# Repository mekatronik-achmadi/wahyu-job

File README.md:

This example test toolkit for various RF module.

###### SIM7000E
- [x] Own VDD
- [x] Serial Comm
- [x] Serial Prog
- [x] SIM Card Slot
- [x] GPS Antena
- [x] RF Antena
- [x] Boot-Config Pin
- [x] USB Firmware (R-USB Optional)
- [x] UART-FT232RL
- [x] UART-ESP32

###### ESP32-WROVER-IB
- [x] Own VDD
- [x] Serial Comm
- [x] Serial Prog
- [x] Boot-Config Pin
- [x] RTS-CTS Transistor
- [x] UART-FT232RL
- [x] UART-SIM7000

###### LORA SX1262
- [ ] Own VDD
- [ ] Serial Comm
- [ ] Serial Prog
- [ ] Boot-Config Pin

###### SIM800C
- [ ] Own VDD
- [ ] Serial Comm
- [ ] Serial Prog
- [ ] GPS Antena
- [ ] RF Antena
- [ ] Boot-Config Pin

###### FT232RL
- [x] Global VDD
- [x] Serial Comm
- [x] USB Port
- [x] UART Indicator (Optional)

###### AMS1117-3V3
- [x] Global VDD
- [x] Global VCC
- [x] VDD Selector

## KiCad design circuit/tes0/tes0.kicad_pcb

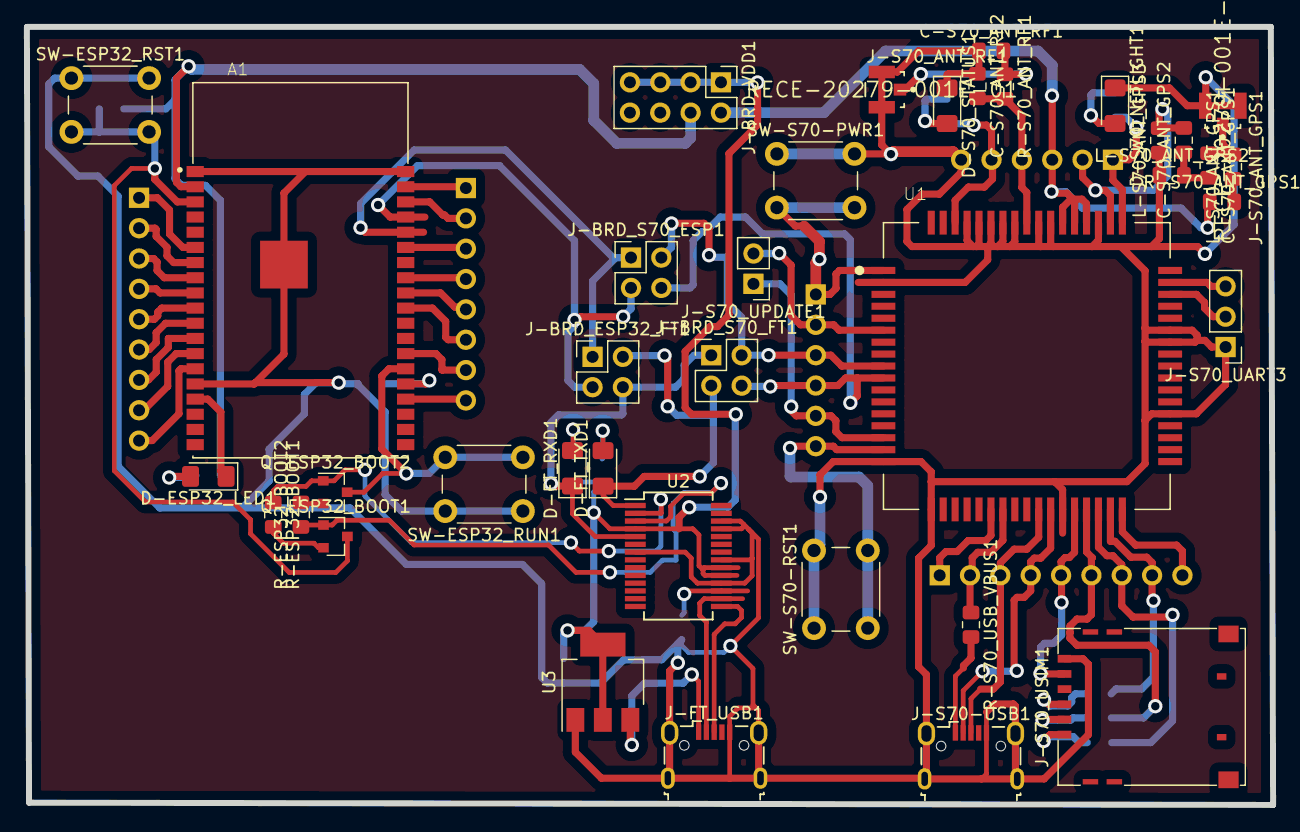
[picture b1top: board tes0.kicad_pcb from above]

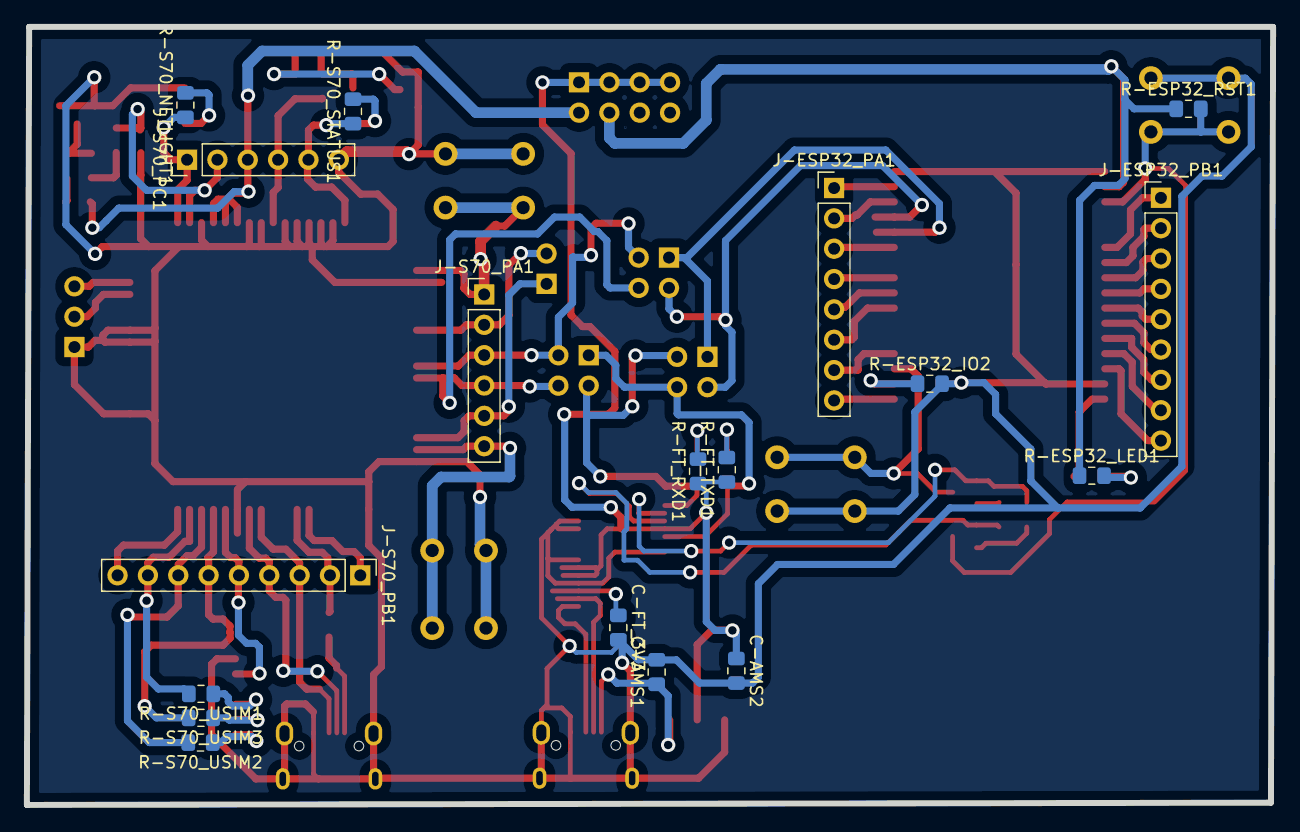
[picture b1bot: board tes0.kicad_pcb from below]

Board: 2 copper layers, 104.3 x 65.1 mm, 56 parts (18 on the bottom side), 71 nets.

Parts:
A1: ESP32-WROVER-I; XCVR_ESP32-WROVER-I
C-AMS1, C-AMS2: 100nF; C_0805_2012Metric_Pad1.15x1.40mm_HandSolder
C-FT_3V3: 100nF; C_0805_2012Metric_Pad1.15x1.40mm_HandSolder
C-S70_ANT_GPS1, C-S70_ANT_GPS2: 33pF; C_0805_2012Metric_Pad1.15x1.40mm_HandSolder
C-S70_ANT_RF1, C-S70_ANT_RF2: C; C_0805_2012Metric_Pad1.15x1.40mm_HandSolder
D-ESP32_LED1: LED; LED_1206_3216Metric_Pad1.42x1.75mm_HandSolder
D-FT_RXD1: LED; LED_1206_3216Metric_Pad1.42x1.75mm_HandSolder
D-FT_TXD1: LED; LED_1206_3216Metric_Pad1.42x1.75mm_HandSolder
D-S70_NETLIGHT1, D-S70_STATUS1: LED; LED_1206_3216Metric_Pad1.42x1.75mm_HandSolder
J-BRD_ESP32_FT1: Conn_02x02_Odd_Even; PinHeader_2x02_P2.54mm_Vertical
J-BRD_S70_ESP1, J-BRD_S70_FT1: Conn_02x02_Odd_Even; PinHeader_2x02_P2.54mm_Vertical
J-BRD_VDD1: Conn_02x04_Odd_Even; PinHeader_2x04_P2.54mm_Vertical
J-ESP32_PA1: Conn_01x08; PinHeader_1x08_P2.54mm_Vertical
J-ESP32_PB1: Conn_01x09; PinHeader_1x09_P2.54mm_Vertical
J-FT_USB1: USB_B_Micro; USB_Micro-B_Wuerth_629105150521
J-S70-USB1: USB_B_Micro; USB_Micro-B_Wuerth_629105150521
J-S70_ANT_GPS1, J-S70_ANT_RF1: RECE-20279-001E-01; Taoglas-RECE-20279-001E-01-MFG
J-S70_PA1, J-S70_PC1: Conn_01x06; PinHeader_1x06_P2.54mm_Vertical
J-S70_PB1: Conn_01x09; PinHeader_1x09_P2.54mm_Vertical
J-S70_UART3: Conn_01x03; PinHeader_1x03_P2.54mm_Vertical
J-S70_UPDATE1: Conn_01x02; PinHeader_1x02_P2.54mm_Vertical
J-S70_USIM1: SIM_Card; microSIM_JAE_SF53S006VCBR2000
L-S70_ANT_GPS1: 47nH; L_0805_2012Metric_Pad1.15x1.40mm_HandSolder
L-S70_ANT_GPS2, L-S70_ANT_GPS3: L; L_0805_2012Metric_Pad1.15x1.40mm_HandSolder
Q-ESP32_BOOT1, Q-ESP32_BOOT2: 2N3904; SOT-23
R-ESP32_BOOT1, R-ESP32_BOOT2: 100; R_0805_2012Metric_Pad1.15x1.40mm_HandSolder
R-ESP32_IO2, R-ESP32_RST1: 10K; R_0805_2012Metric_Pad1.15x1.40mm_HandSolder
R-ESP32_LED1: 330; R_0805_2012Metric_Pad1.15x1.40mm_HandSolder
R-FT_RXD1: 330; R_0805_2012Metric_Pad1.15x1.40mm_HandSolder
R-FT_TXD1: 330; R_0805_2012Metric_Pad1.15x1.40mm_HandSolder
R-S70_ANT_GPS1: 10; R_0805_2012Metric_Pad1.15x1.40mm_HandSolder
R-S70_ANT_RF1, R-S70_USB_VBUS1: 0; R_0805_2012Metric_Pad1.15x1.40mm_HandSolder
R-S70_NETLIGHT1, R-S70_STATUS1: 330; R_0805_2012Metric_Pad1.15x1.40mm_HandSolder
R-S70_USIM1, R-S70_USIM2, R-S70_USIM3: 22; R_0805_2012Metric_Pad1.15x1.40mm_HandSolder
SW-ESP32_RST1, SW-ESP32_RUN1: SW_Push; SW_PUSH_6mm
SW-S70-PWR1, SW-S70-RST1: SW_Push; SW_PUSH_6mm
U1: SIM7000E; SIMCON_SIM7000E
U2: FT232RL; SSOP-28_5.3x10.2mm_P0.65mm
U3: AMS1117-3.3; SOT-223-3_TabPin2

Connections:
/ESP32_BOOT: A1.25, Q-ESP32_BOOT2.3, SW-ESP32_RUN1.2
/ESP32_IO4: A1.26, J-ESP32_PA1.7
/ESP32_IO5: A1.29, J-ESP32_PA1.6
/ESP32_IO12: A1.14, J-ESP32_PB1.9
/ESP32_IO14: A1.13, J-ESP32_PB1.8
/ESP32_IO15: A1.23, J-ESP32_PA1.8
/ESP32_IO18: A1.30, J-ESP32_PA1.5
/ESP32_IO19: A1.31, J-ESP32_PA1.4
/ESP32_IO21: A1.33, J-ESP32_PA1.3
/ESP32_IO22: A1.36, J-ESP32_PA1.2
/ESP32_IO23: A1.37, J-ESP32_PA1.1
/ESP32_IO25: A1.10, J-ESP32_PB1.5
/ESP32_IO26: A1.11, J-ESP32_PB1.6
/ESP32_IO27: A1.12, J-ESP32_PB1.7
/ESP32_IO32: A1.8, J-ESP32_PB1.3
/ESP32_IO33: A1.9, J-ESP32_PB1.4
/ESP32_IO34: A1.6, J-ESP32_PB1.1
/ESP32_IO35: A1.7, J-ESP32_PB1.2
/ESP32_LED: A1.16, D-ESP32_LED1.1
/ESP32_RST: A1.3, Q-ESP32_BOOT1.3, R-ESP32_RST1.2, SW-ESP32_RST1.2
/ESP32_RXD: A1.34, J-BRD_ESP32_FT1.1, J-BRD_S70_ESP1.1
/ESP32_TXD: A1.35, J-BRD_ESP32_FT1.3, J-BRD_S70_ESP1.3
/ESP32_VDD: A1.2, J-BRD_VDD1.4, R-ESP32_LED1.1, R-ESP32_RST1.1
/FT_DTR: Q-ESP32_BOOT2.1, R-ESP32_BOOT1.1, U2.2
/FT_RTS: Q-ESP32_BOOT1.1, R-ESP32_BOOT2.1, U2.3
/FT_RXD: D-FT_RXD1.1, J-BRD_ESP32_FT1.4, J-BRD_S70_FT1.1, U2.5
/FT_TXD: D-FT_TXD1.1, J-BRD_ESP32_FT1.2, J-BRD_S70_FT1.3, U2.1
/S70_ANT_GPS: C-S70_ANT_GPS2.2, J-S70_PC1.2, L-S70_ANT_GPS3.2, U1.53
/S70_ANT_RF: C-S70_ANT_RF2.2, J-S70_PC1.4, R-S70_ANT_RF1.2, U1.60
/S70_BOOTCFG: J-S70_PA1.2, J-S70_UPDATE1.2, U1.6
/S70_GPIO0: J-S70_UART3.3, U1.50
/S70_GPIO1: J-S70_UART3.2, U1.49
/S70_MDMLOG_TX: J-S70_PB1.1, U1.23
/S70_NETLIGHT: J-S70_PC1.1, R-S70_NETLIGHT1.1, U1.52
/S70_NRST: J-S70_PA1.6, SW-S70-RST1.2, U1.16
/S70_PWRKEY: J-S70_PA1.1, SW-S70-PWR1.2, U1.1
/S70_RXD: J-BRD_S70_ESP1.4, J-BRD_S70_FT1.4, J-S70_PA1.4, U1.10
/S70_STATUS: J-S70_PC1.5, R-S70_STATUS1.1, U1.66
/S70_TXD: J-BRD_S70_ESP1.2, J-BRD_S70_FT1.2, J-S70_PA1.3, U1.9
/S70_USB_DM: J-S70-USB1.2, J-S70_PB1.4, U1.28
/S70_USB_DP: J-S70-USB1.3, J-S70_PB1.3, U1.27
/S70_USB_VBUS: J-S70_PB1.2, R-S70_USB_VBUS1.1, U1.24
/S70_USIM_CLK: J-S70_PB1.7, R-S70_USIM2.2, U1.32
/S70_USIM_DATA: J-S70_PB1.6, R-S70_USIM3.2, U1.31
/S70_USIM_DET: J-S70_PB1.9, U1.34
/S70_USIM_RST: J-S70_PB1.8, R-S70_USIM1.2, U1.33
/S70_USIM_VDD: J-S70_PB1.5, J-S70_USIM1.1, U1.30
/S70_VDD: J-BRD_VDD1.2, J-S70_PC1.3, R-S70_ANT_GPS1.1, U1.55, U1.56, U1.57
/S70_VDDEXT: J-S70_PA1.5, J-S70_UPDATE1.1, U1.15
GND: A1.1, A1.15, A1.38, A1.39, C-AMS1.2, C-AMS2.2, C-FT_3V3.2, C-S70_ANT_RF1.1, C-S70_ANT_RF2.1, D-S70_NETLIGHT1.1, D-S70_STATUS1.1, J-FT_USB1.5, J-FT_USB1.6, J-S70-USB1.5, J-S70-USB1.6, J-S70_ANT_GPS1.2, J-S70_ANT_GPS1.3, J-S70_ANT_RF1.2, J-S70_ANT_RF1.3, J-S70_PC1.6, J-S70_UART3.1, J-S70_USIM1.5, L-S70_ANT_GPS2.1, L-S70_ANT_GPS3.1, R-ESP32_IO2.2, SW-ESP32_RST1.1, SW-ESP32_RUN1.1, SW-S70-PWR1.1, SW-S70-RST1.1, U1.2, U1.17, U1.18, U1.29, U1.39, U1.45, U1.46, U1.54, U1.58, U1.59, U1.61, U1.62, U1.63, U1.64, U1.65, U2.7, U2.18, U2.21, U2.25, U2.26, U3.1
unnamed: A1.24, R-ESP32_IO2.1
unnamed: C-FT_3V3.1, U2.17
unnamed: C-S70_ANT_GPS1.1, J-S70_ANT_GPS1.1, L-S70_ANT_GPS1.2
unnamed: C-S70_ANT_GPS1.2, C-S70_ANT_GPS2.1, L-S70_ANT_GPS2.2
unnamed: C-S70_ANT_RF1.2, J-S70_ANT_RF1.1, R-S70_ANT_RF1.1
unnamed: D-ESP32_LED1.2, R-ESP32_LED1.2
unnamed: D-FT_RXD1.2, R-FT_TXD1.2
unnamed: D-FT_TXD1.2, R-FT_RXD1.2
unnamed: D-S70_NETLIGHT1.2, R-S70_NETLIGHT1.2
unnamed: D-S70_STATUS1.2, R-S70_STATUS1.2
unnamed: J-FT_USB1.2, U2.16
unnamed: J-FT_USB1.3, U2.15
unnamed: J-S70-USB1.1, R-S70_USB_VBUS1.2
unnamed: J-S70_USIM1.2, R-S70_USIM1.1
unnamed: J-S70_USIM1.3, R-S70_USIM2.1
unnamed: J-S70_USIM1.7, R-S70_USIM3.1
unnamed: L-S70_ANT_GPS1.1, R-S70_ANT_GPS1.2
unnamed: Q-ESP32_BOOT1.2, R-ESP32_BOOT1.2
unnamed: Q-ESP32_BOOT2.2, R-ESP32_BOOT2.2
VCC: C-AMS1.1, J-FT_USB1.1, U3.3
VDD: C-AMS2.1, J-BRD_VDD1.1, J-BRD_VDD1.3, J-BRD_VDD1.5, J-BRD_VDD1.7, R-FT_RXD1.1, R-FT_TXD1.1, U2.4, U2.19, U2.20, U3.2

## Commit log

2020-10-22 init
2020-10-22 init readme
2020-10-22 sim7000e basic
2020-10-22 sim7000e minus antena
2020-10-23 add FT232RL
2020-10-24 update ikut skematik datasheet
2020-10-25 new lib
2020-10-25 basic ESP32+SIM7000
